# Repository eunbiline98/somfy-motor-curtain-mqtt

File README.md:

# somfy-motor-curtain-mqtt
DIY Motorize Curtain Somfy Control Using Esp8266 MQTT Protocol
- Motorize Curtain Somfy Glydea                                       

Datasheet Motorize Curtain                                                     
- 
- https://www.somfypro.ca/documents/3931489/18635940/Glydea-Databook.pdf

List Item

- Esp8266 (Wemos D1 Mini)
- Optocoupler PC817
- Power Module Hi-Link 220VAC to 5VDC
- Resistor 1k 1/4 Watt
- Terminal Screw 2 Pin Hole

# Schematic

# Control
- Open Curtain
- Close Curtain
- Stop Curtain

# Home Assistant Setup 

Under covers in HA, use this config Motorize Curtain Control
```
  - platform: mqtt
    name: "Curtain Living Room"
    command_topic: "home/curtain/livingroom"
    state_topic: "home/curtain/state"
    qos: 0
    retain: true
    payload_open: "u"
    payload_close: "d"
    payload_stop: "s"
    state_open: "open"
    state_opening: "opening"
    state_closed: "closed"
    state_closing: "closing"
    optimistic: false
```

Under covers in HA, use this config MQTT

```
mqtt:
  broker: "Your IP Broker/server"
  port: Your port MQTT
  username: "Your username"
  password: Your password
  
```

# Documentation
https://user-images.githubusercontent.com/50385294/149776929-379bbfac-4cdb-4a9a-a8d9-ceeab45c952e.mp4

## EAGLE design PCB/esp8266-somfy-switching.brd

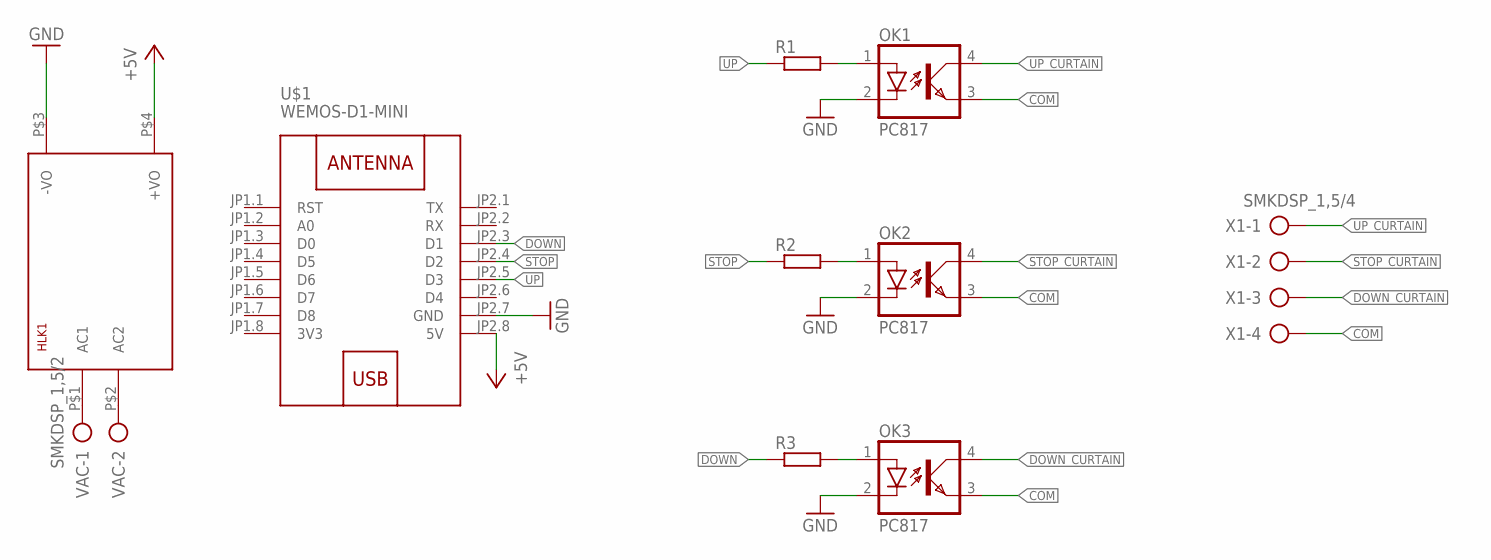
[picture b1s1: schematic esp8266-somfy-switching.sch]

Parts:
HLK1: HLK-PM013W; HLK-PM01
OK1, OK2, OK3: PC817; DIL04
R1, R2, R3: R-EU_0207/10; 0207/10
U$1: WEMOS-D1-MINI
VAC: SMKDSP_1,5/2
X1: SMKDSP_1,5/4

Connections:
3V3: U$1.JP1.8 (3V3)
+5V: HLK1.P$4 (+VO), U$1.JP2.8 (5V)
COM: OK1.3 (EMIT), OK2.3 (EMIT), OK3.3 (EMIT), X1.4
DOWN: R3.1, U$1.JP2.3 (D1)
DOWN_CURTAIN: OK3.4 (COL), X1.3
GND: HLK1.P$3 (-VO), OK1.2 (C), OK2.2 (C), OK3.2 (C), U$1.JP2.7 (GND)
unnamed: HLK1.P$1 (AC1), VAC.1
unnamed: HLK1.P$2 (AC2), VAC.2
unnamed: OK1.1 (A), R1.2
unnamed: OK2.1 (A), R2.2
unnamed: OK3.1 (A), R3.2
STOP: R2.1, U$1.JP2.4 (D2)
STOP_CURTAIN: OK2.4 (COL), X1.2
UP: R1.1, U$1.JP2.5 (D3)
UP_CURTAIN: OK1.4 (COL), X1.1

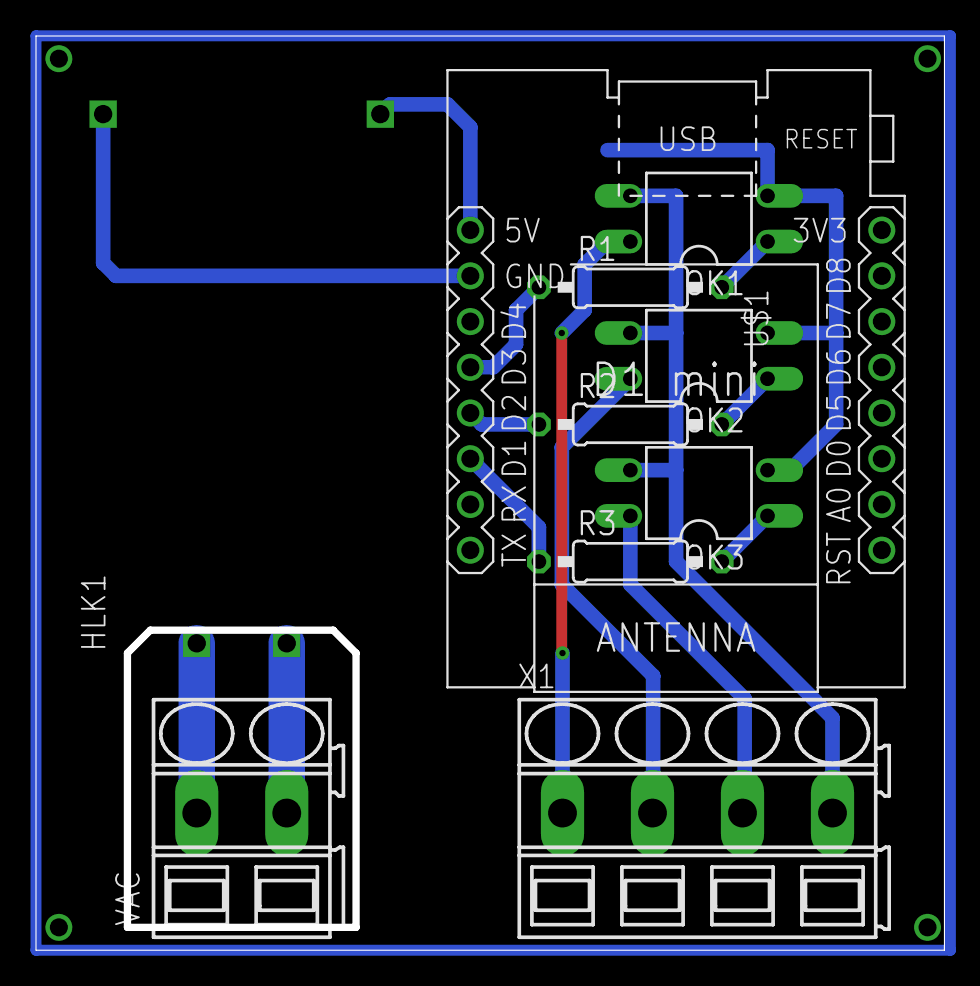
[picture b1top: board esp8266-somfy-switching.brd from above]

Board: 2 copper layers, 50.5 x 50.8 mm, 10 parts (0 on the bottom side), 14 nets.

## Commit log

2022-01-12 Adding Program V1.0
    Connect MQTT,WiFi Manager
2022-01-12 Upload PCB Design
2022-01-12 Upload Schematic Design
2022-01-12 Adding Schematic
2022-01-17 Adding Doc

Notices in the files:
parts and their libraries:
diy-modules: Released under the Creative Commons Attribution 4.0 International License: http://creativecommons.org/licenses/by/4.0
